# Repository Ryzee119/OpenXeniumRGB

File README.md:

# OpenXeniumRGB
RGB Addon Board for the OpenXenium modchip. Should also work on Genuine Xenium modchips.
Also see [OpenXenium](https://github.com/Ryzee119/OpenXenium).

## PCB
When fabricating your own, you can download the premade gerbers from the `Release` section or generate your own. Suggested PCB properties are:  <br>
`2 layers, 35x20mm, 1.0mm thick, HASL, 1oz copper, no castellated holes, any colour you want!`<br>

## Bill of Materials

| Qty | Value/Model | Description | Marking | URL |
| --- | --- | --- | --- | --- |
| 1 | 19-237/R6GHBHC-A07/2T | LED RGB CLEAR 4SMD. COMMON ANODE | LED1 | https://www.digikey.com.au/short/p2475q |
| 3 | RK73B1JTTD680J | RES 68 OHM 5% 1/8W 0603 | R1,R2,R3 | https://www.digikey.com.au/short/p247rp |
| 1 | SHR-10V-S-B |JST SH1.0 10 pin 1mm connector (To connect to Xenium)| - |Digikey: [Connector](https://www.digikey.com.au/product-detail/en/jst-sales-america-inc/SHR-10V-S-B/455-1385-ND/759874) + 3x[Jumpers](https://www.digikey.com.au/product-detail/en/jst-sales-america-inc/ASSHSSH28K152/455-3076-ND/6009452) OR <br> Aliexpress: [Connector with Jumpers (Get the 10P one)](https://www.aliexpress.com/item/5PCS-100MM-SH-1-0-Wire-Cable-Connector-DIY-SH1-0-JST-2-3-4-5/32952366214.html) |

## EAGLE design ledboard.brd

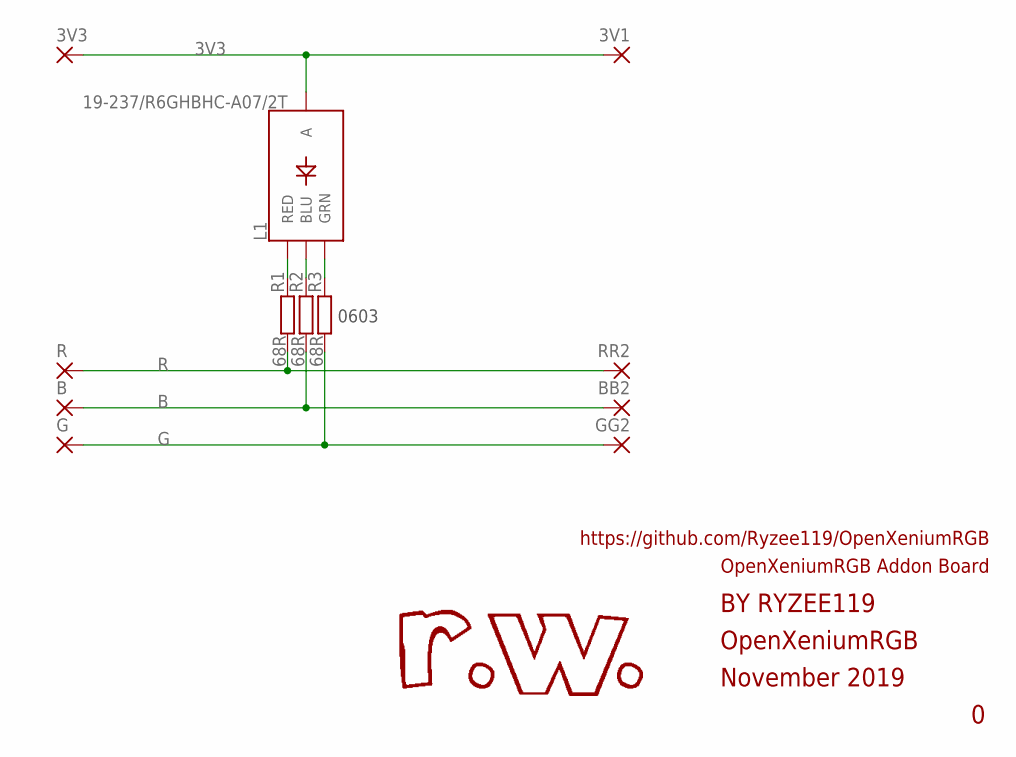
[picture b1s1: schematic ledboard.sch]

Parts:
3V1, 3V3: SMD2; SMD1,27-2,54
B: SMD2; SMD1,27-2,54
BB2: SMD2; SMD1,27-2,54
G: SMD2; SMD1,27-2,54
GG2: SMD2; SMD1,27-2,54
L1: 19-237/R6GHBHC-A07/2T; 4-SMD-R6GHBHC
R: SMD2; SMD1,27-2,54
R1, R2, R3: 68R; R0603
RR2: SMD2; SMD1,27-2,54

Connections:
3V3: 3V1.1, 3V3.1, L1.P$2 (A)
B: B.1, BB2.1, R2.1
BLUE: L1.P$4 (BLU), R2.2
G: G.1, GG2.1, R3.1
GREEN: L1.P$3 (GRN), R3.2
R: R.1, R1.1, RR2.1
RED: L1.P$1 (RED), R1.2

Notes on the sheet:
0603
OpenXeniumRGB
November 2019
BY RYZEE119
OpenXeniumRGB Addon Board
https://github.com/Ryzee119/OpenXeniumRGB

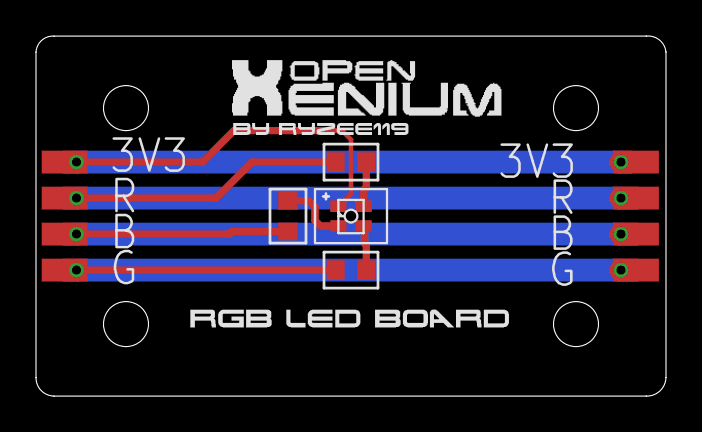
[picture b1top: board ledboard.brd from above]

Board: 2 copper layers, 35.0 x 20.0 mm, 12 parts (0 on the bottom side), 7 nets.

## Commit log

2019-11-11 Create LICENSE
